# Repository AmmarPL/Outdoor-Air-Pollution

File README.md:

# Embedded System for Air Quality Measurement

This project involves the design and implementation of an embedded system to measure air quality, with a focus on particulate matter (PM10) concentrations. It was specifically developed and tested during Diwali in 2019, when air pollution levels are known to spike significantly due to fireworks and other festivities.

# Overview
The air quality measurement device uses an ESP8266 microcontroller to gather data from various sensors and transmit it to a Python Flask server using oneM2M. The data is then visualized and analyzed through Thingspeak, showcasing significant spikes in PM10 levels, particularly around student residential areas. The entire circuit was designed using EagleCAD.

# Features
Sensor Integration: Incorporates multiple sensors to measure various pollutants, with a focus on PM10 particulate matter.

Connectivity: Uses an ESP8266 microcontroller for processing sensor data and providing Wi-Fi connectivity.

Data Handling: Transmits data to a Python Flask server, which is then pushed to Thingspeak for analysis and visualization.

EagleCAD Design: Custom PCB design for neatly organized and efficient sensor integration and microcontroller setup.

# Results
We found that some of the air quality indicators had a bad spike around Diwali.

We also found that these spikes were concentrated around the student residences. 

Both these plots are for PM10, but similar spikes were found in PM2.5 and CO, but not with NH3 and NO2.

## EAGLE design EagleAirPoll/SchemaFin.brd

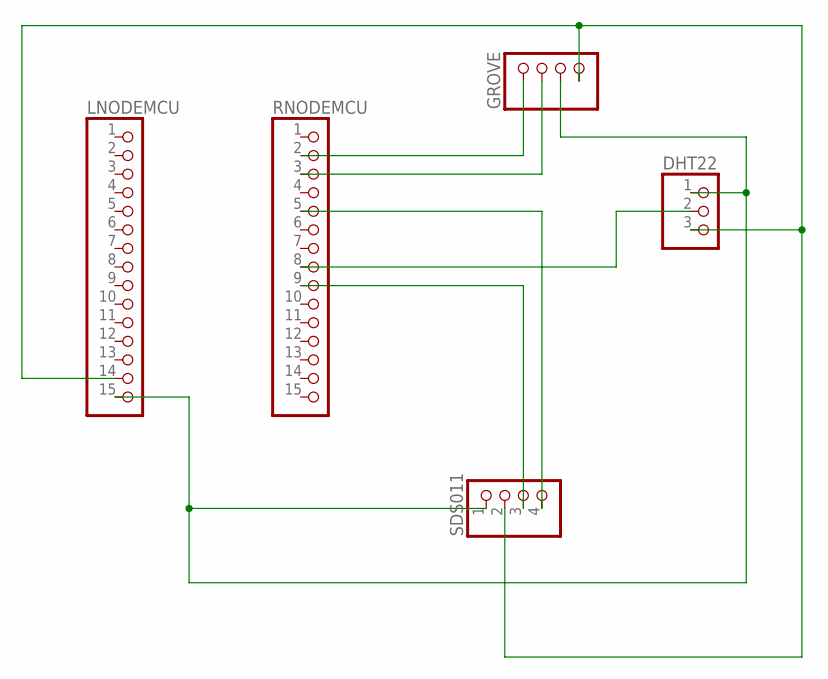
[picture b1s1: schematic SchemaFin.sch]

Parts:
DHT22: PINHD-1X3; 1X03
GROVE: PINHD-1X4M; 1X04M
LNODEMCU: PINHD-1X15; 1X15
RNODEMCU: PINHD-1X15; 1X15
SDS011: PINHD-1X4; 1X04

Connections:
unnamed: GROVE.1, RNODEMCU.2
unnamed: GROVE.2, RNODEMCU.3
unnamed: RNODEMCU.5, SDS011.4
unnamed: DHT22.2, RNODEMCU.8
unnamed: RNODEMCU.9, SDS011.3
unnamed: DHT22.1, GROVE.3, LNODEMCU.15, SDS011.1
unnamed: DHT22.3, GROVE.4, LNODEMCU.14, SDS011.2

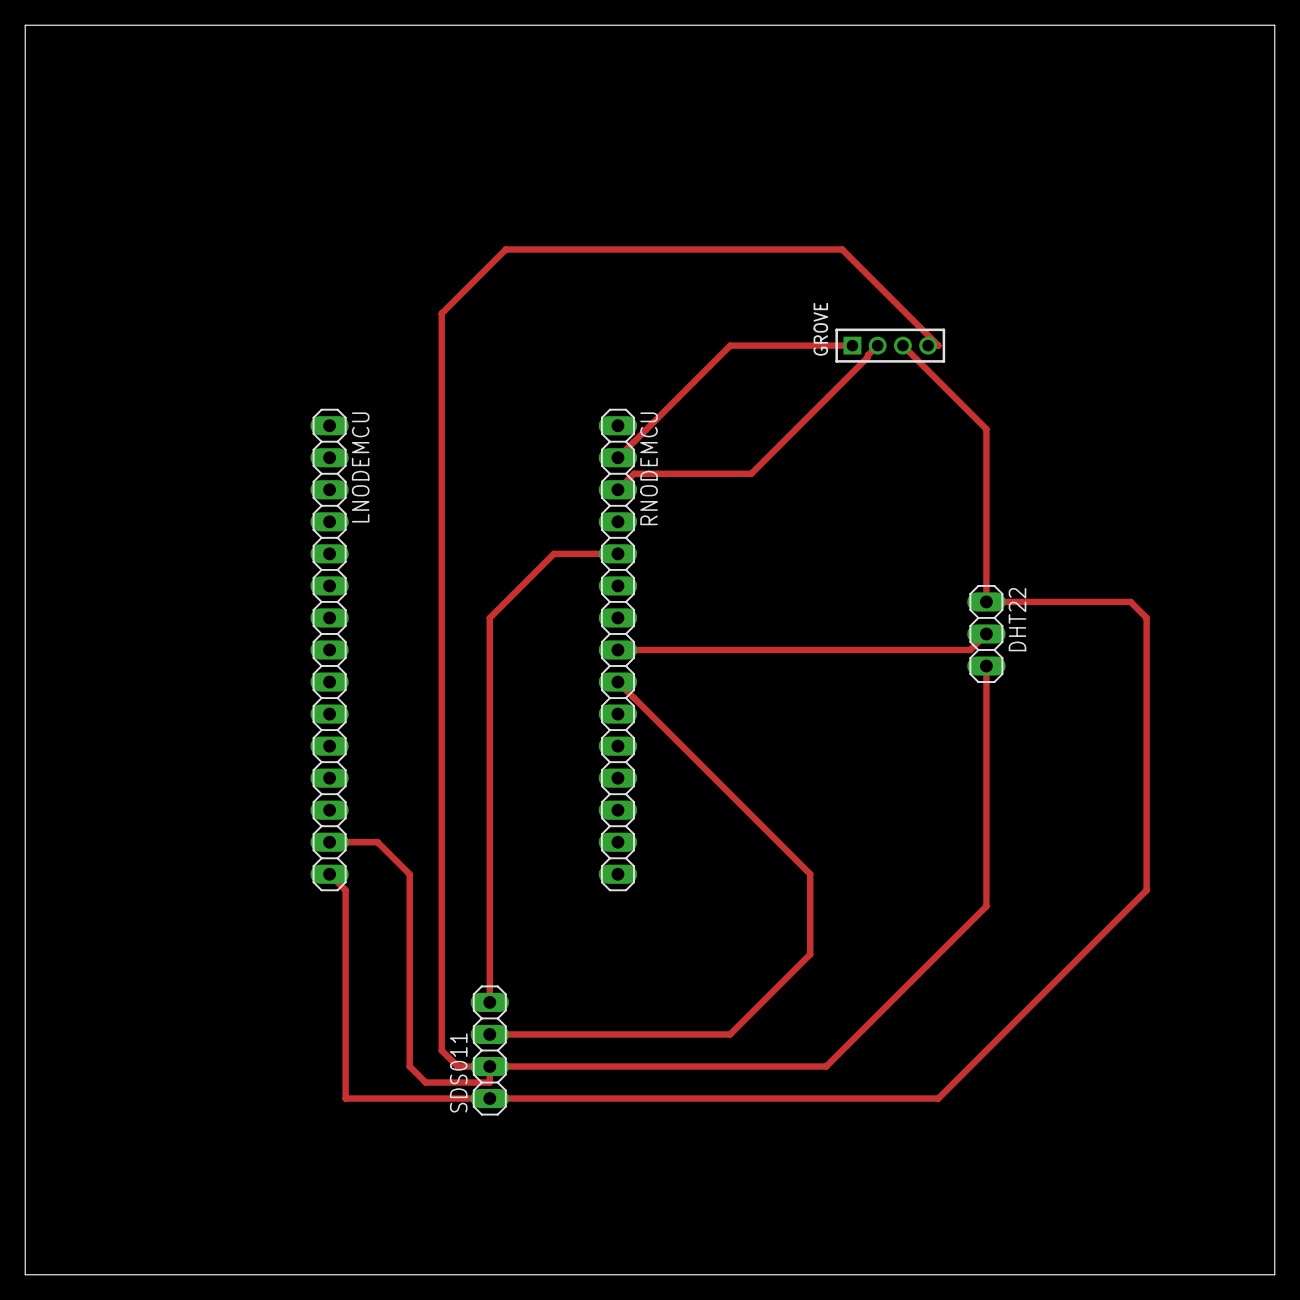
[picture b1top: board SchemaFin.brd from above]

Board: 2 copper layers, 99.1 x 99.1 mm, 5 parts (0 on the bottom side), 7 nets.

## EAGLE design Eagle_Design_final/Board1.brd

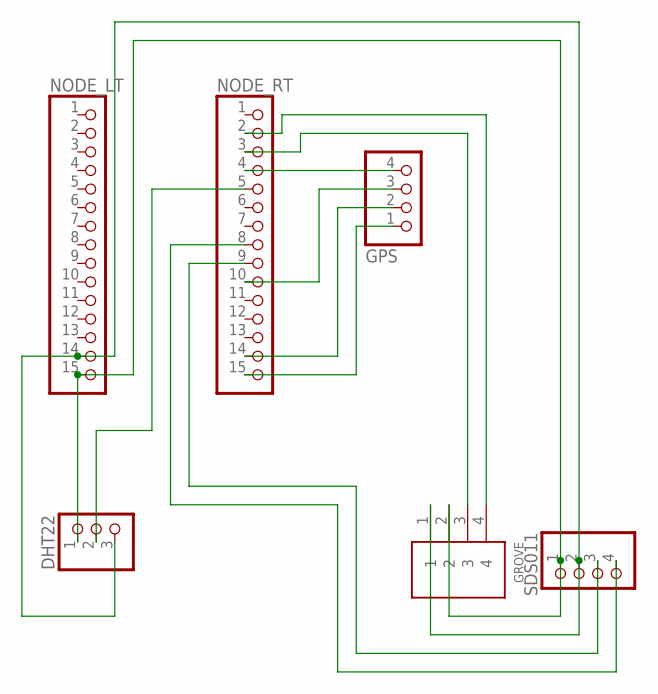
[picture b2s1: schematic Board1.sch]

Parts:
DHT22: PINHD-1X3; 1X03
GPS: PINHD-1X4; 1X04
GROVE: 4PIN; B4B-PH-K-S
NODE_LT: PINHD-1X15; 1X15
NODE_RT: PINHD-1X15; 1X15
SDS011: PINHD-1X4; 1X04

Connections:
unnamed: DHT22.1, GROVE.2, NODE_LT.15, SDS011.1
unnamed: DHT22.3, GROVE.1, NODE_LT.14, SDS011.2
unnamed: GPS.4, NODE_RT.4
unnamed: GPS.3, NODE_RT.10
unnamed: DHT22.2, NODE_RT.5
unnamed: NODE_RT.9, SDS011.3
unnamed: GPS.2, NODE_RT.14
unnamed: GROVE.3, NODE_RT.3
unnamed: GROVE.4, NODE_RT.2
unnamed: GPS.1, NODE_RT.15
unnamed: NODE_RT.8, SDS011.4

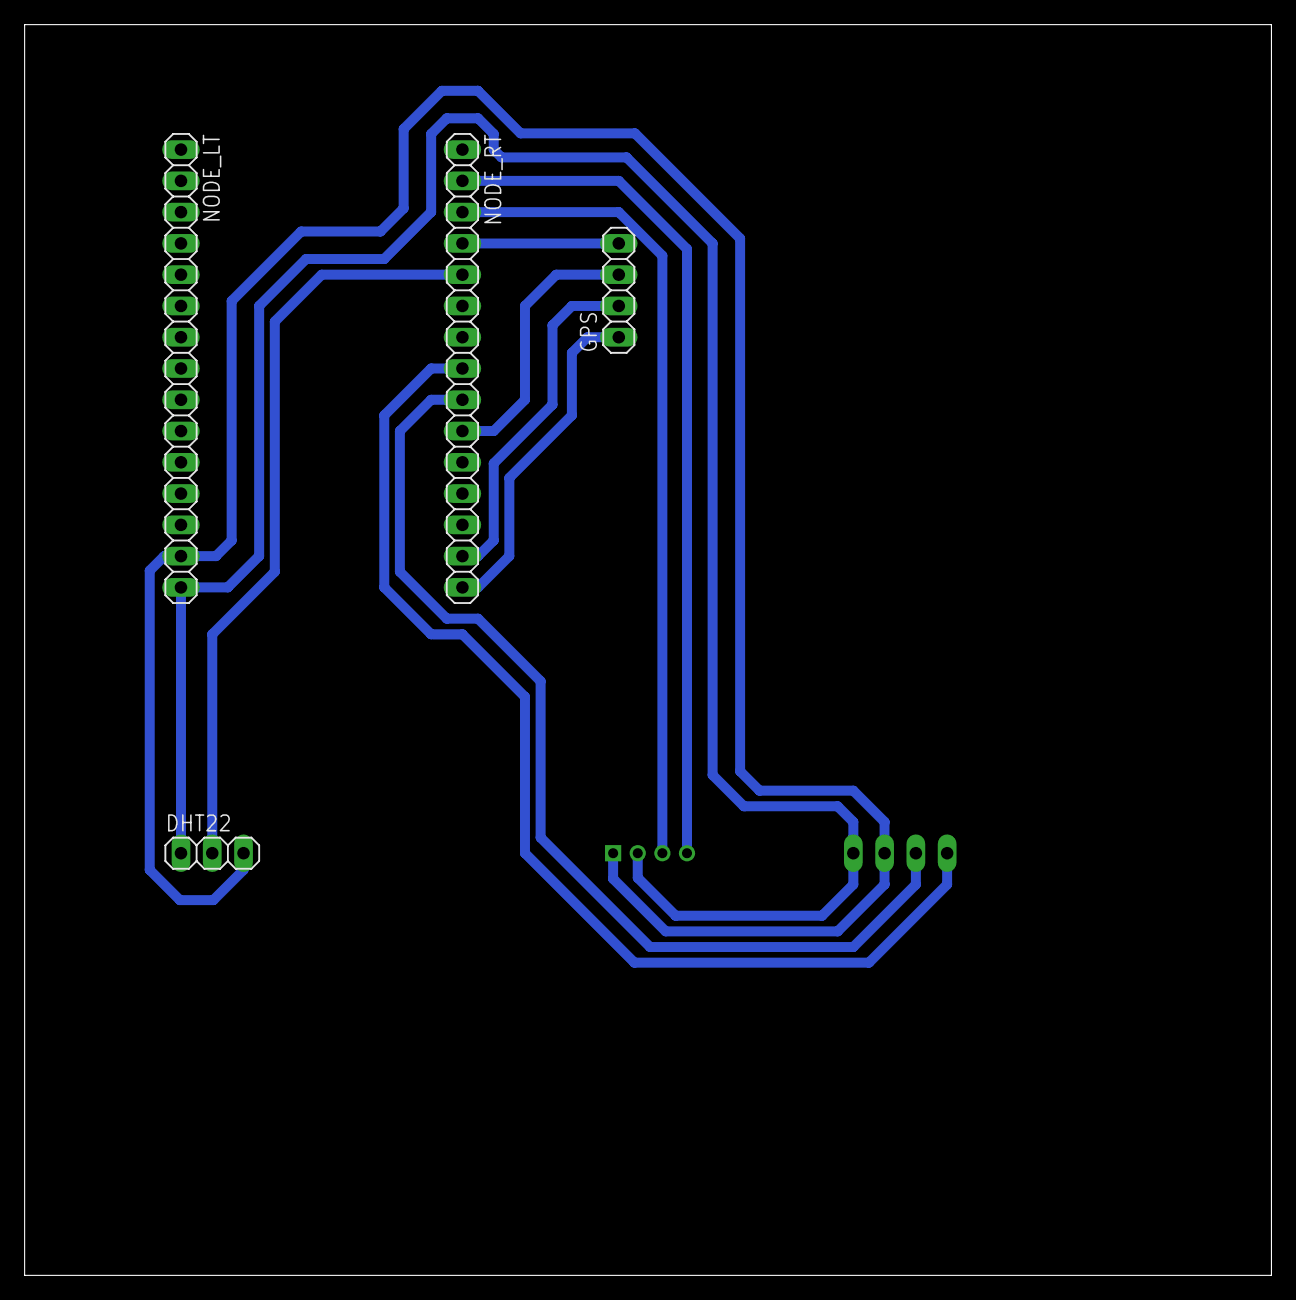
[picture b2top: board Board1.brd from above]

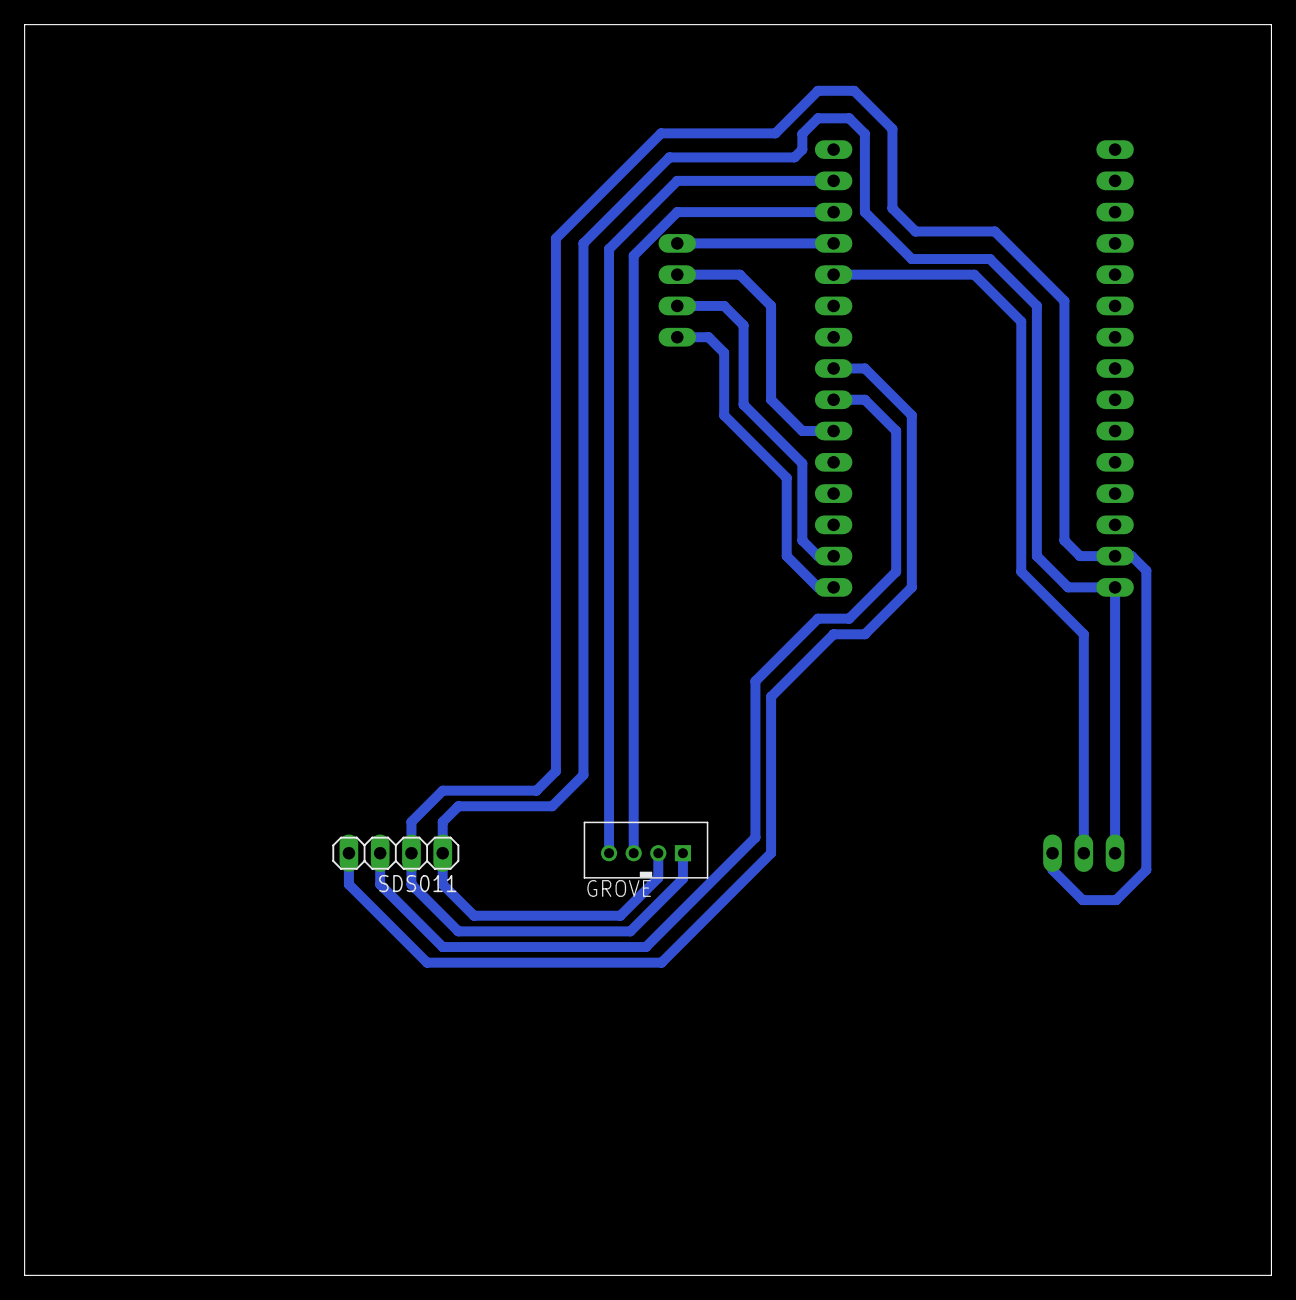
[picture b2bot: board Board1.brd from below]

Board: 2 copper layers, 101.3 x 101.6 mm, 6 parts (2 on the bottom side), 11 nets.

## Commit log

2019-10-03 Added files
2019-10-07 Put Eagle files in the folder
2019-10-07 Remove consistency errors
2019-10-07 Modify Board
2019-10-10 Updated Final Code, Added Final Eagle Board Schematics, Added OneM2M code
2019-10-18 Seperated code for both nodes
2019-11-24 Added most things
2019-11-24 All commit
2019-11-25 Final commit
2019-11-25 Fixed colors
2019-12-14 Create ThingSpeakCredentials
